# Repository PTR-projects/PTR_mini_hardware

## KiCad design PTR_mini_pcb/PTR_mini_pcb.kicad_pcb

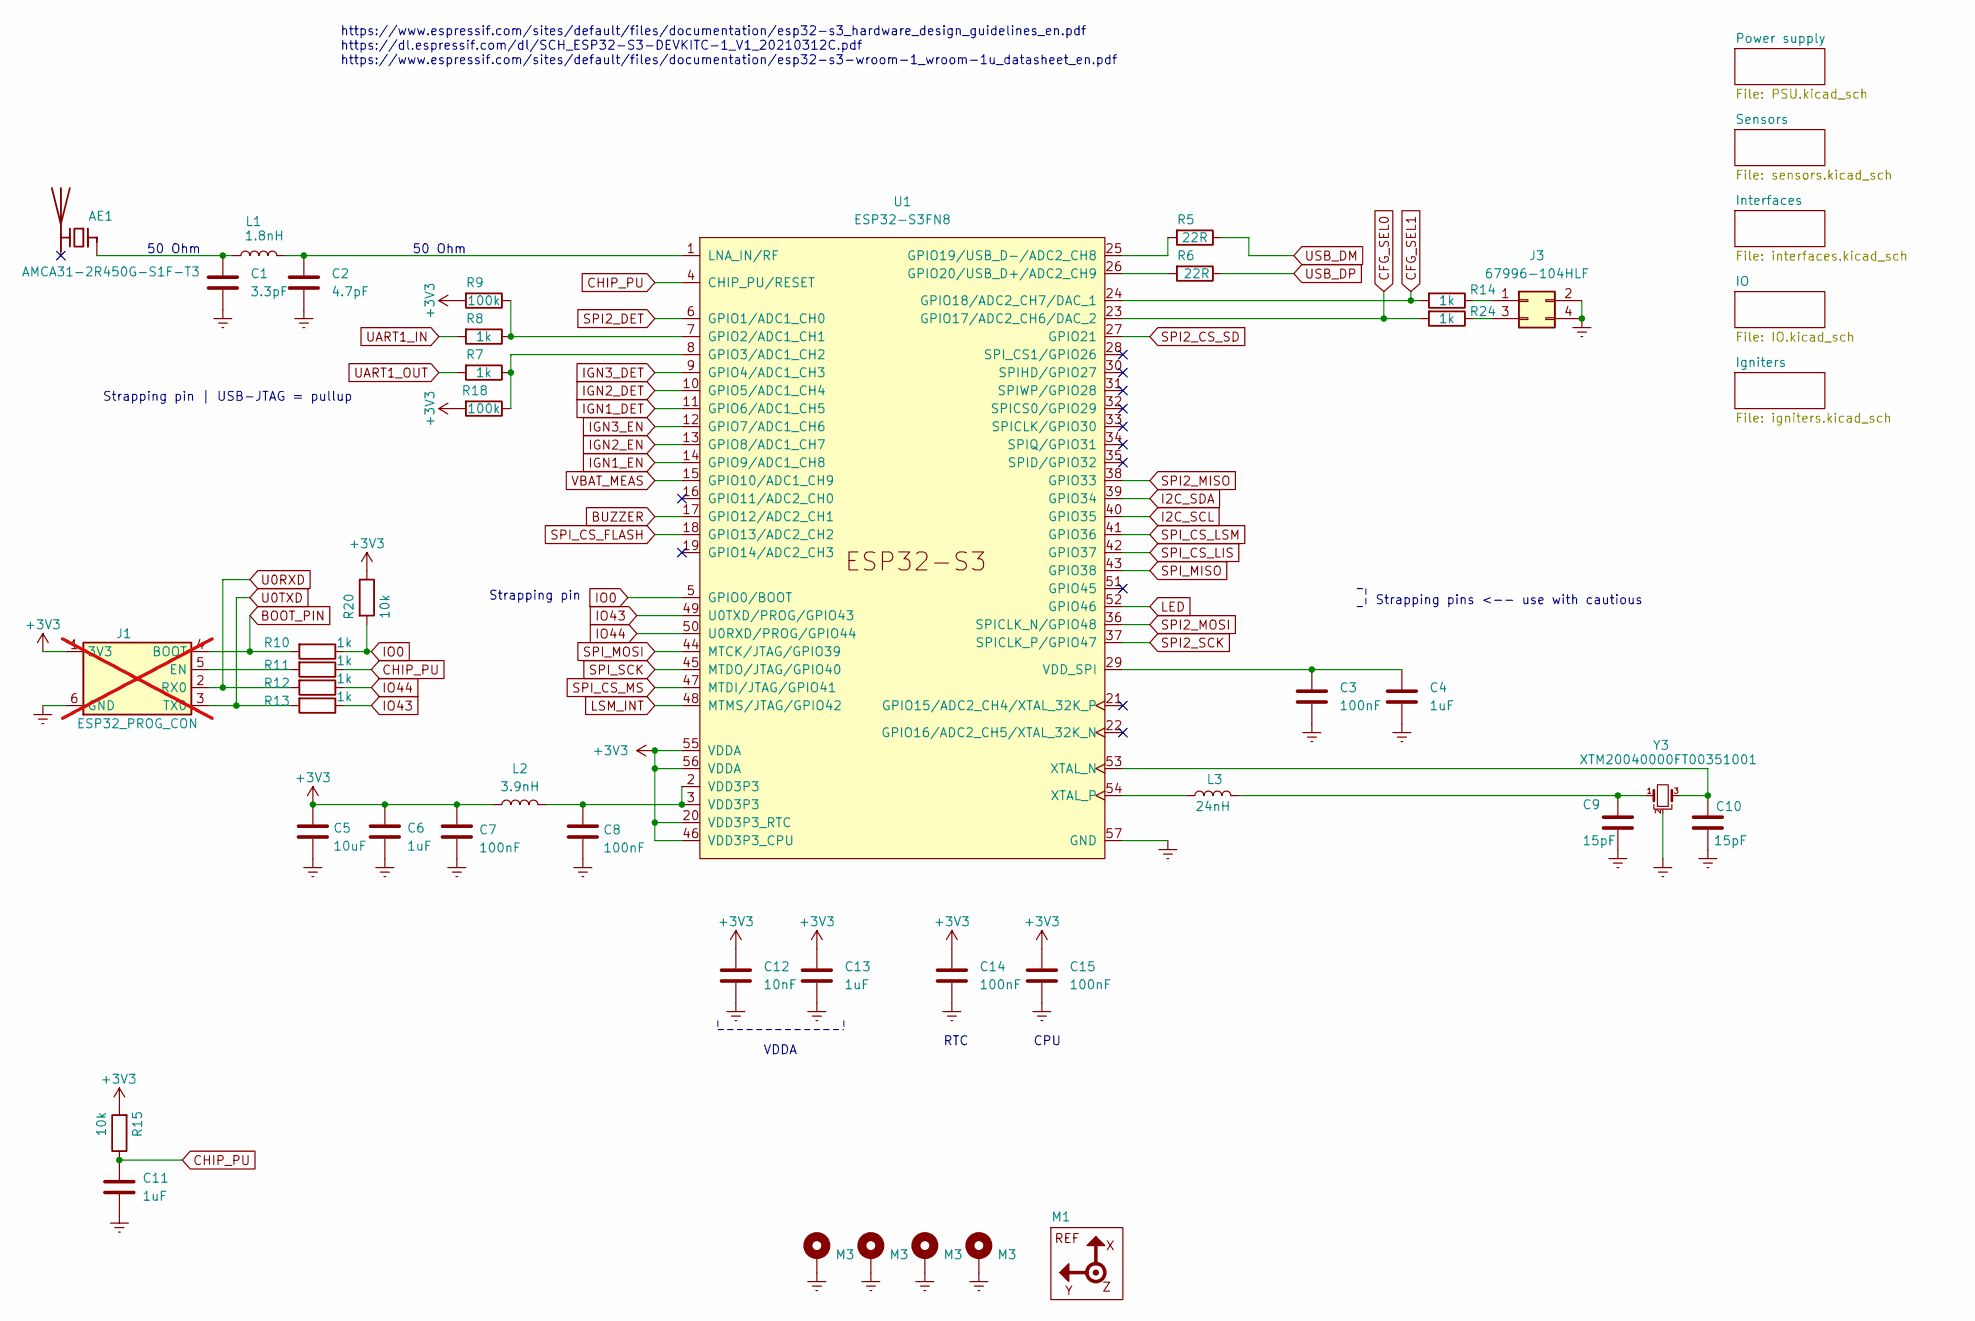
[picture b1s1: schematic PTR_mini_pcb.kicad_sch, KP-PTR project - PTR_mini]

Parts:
AE1: AMCA31-2R450G-S1F-T3
C1: 3.3pF; C_0402_1005Metric
C2: 4.7pF; C_0402_1005Metric
C3, C7, C8, C14, C15: 100nF; C_0402_1005Metric
C4, C6, C11, C13: 1uF; C_0402_1005Metric
C5: 10uF; C_0603_1608Metric
C9, C10: 15pF; C_0402_1005Metric
C12: 10nF; C_0402_1005Metric
H1, H2, H3, H4: M3; MountingHole_3.2mm_M3_DIN965_Pad
J1: ESP32_PROG_CON; PinHeader_1x06_P1.27mm_Vertical; not fitted
J3: 67996-104HLF; PinHeader_2x02_P2.54mm_Vertical
L1: 1.8nH; L_0402_1005Metric
L2: 3.9nH; L_0402_1005Metric
L3: 24nH; L_0402_1005Metric
M1: Reference_frame
R5, R6: 22R; R_0402_1005Metric
R7, R8, R10, R11, R12, R13, R14, R24: 1k; R_0402_1005Metric
R9, R18: 100k; R_0402_1005Metric
R15, R20: 10k; R_0402_1005Metric
U1: ESP32-S3FN8; ESP32-S3
Y3: XTM20040000FT00351001; Crystal_SMD_2016-4Pin_2.0x1.6mm

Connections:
+3V3: C5.1, C6.1, C7.1, C12.1, C13.1, C14.1, C15.1, J1.1 (3V3), L2.1, R9.2, R15.2, R18.2, R20.1, U1.20 (VDD3P3_RTC), U1.46 (VDD3P3_CPU), U1.55 (VDDA), U1.56 (VDDA); also elsewhere on the board
BOOT_PIN: J1.4 (BOOT), R10.2
BUZZER: U1.17 (GPIO12/ADC2_CH1); also elsewhere on the board
CFG_SEL0: R24.2, U1.23 (GPIO17/ADC2_CH6/DAC_2)
CFG_SEL1: R14.2, U1.24 (GPIO18/ADC2_CH7/DAC_1)
CHIP_PU: C11.2, R11.1, R15.1, U1.4 (CHIP_PU/RESET)
Earth: C1.2, C2.2, C3.2, C4.2, C5.2, C6.2, C7.2, C8.2, C9.1, C10.2, C11.1, C12.2, C13.2, C14.2, C15.2, H1.1 (1_1), H2.1 (1_1), H3.1 (1_1), H4.1 (1_1), J1.6 (GND), J3.2, J3.4, U1.57 (GND), Y3.2, Y3.4; also elsewhere on the board
I2C_SCL: U1.40 (GPIO35); also elsewhere on the board
I2C_SDA: U1.39 (GPIO34); also elsewhere on the board
IGN1_DET: U1.11 (GPIO6/ADC1_CH5); also elsewhere on the board
IGN1_EN: U1.14 (GPIO9/ADC1_CH8); also elsewhere on the board
IGN2_DET: U1.10 (GPIO5/ADC1_CH4); also elsewhere on the board
IGN2_EN: U1.13 (GPIO8/ADC1_CH7); also elsewhere on the board
IGN3_DET: U1.9 (GPIO4/ADC1_CH3); also elsewhere on the board
IGN3_EN: U1.12 (GPIO7/ADC1_CH6); also elsewhere on the board
IO0: R10.1, R20.2, U1.5 (GPIO0/BOOT)
IO43: R13.1, U1.49 (U0TXD/PROG/GPIO43)
IO44: R12.1, U1.50 (U0RXD/PROG/GPIO44)
LED: U1.52 (GPIO46); also elsewhere on the board
LSM_INT: U1.48 (MTMS/JTAG/GPIO42); also elsewhere on the board
unnamed: AE1.1 (FEED_1), C1.1, L1.1
unnamed: C8.1, L2.2, U1.2 (VDD3P3), U1.3 (VDD3P3)
unnamed: C9.2, L3.2, Y3.1
unnamed: J1.5 (EN), R11.2
unnamed: J3.1, R14.1
unnamed: J3.3, R24.1
unnamed: R8.1, R9.1, U1.7 (GPIO2/ADC1_CH1)
unnamed: R7.1, R18.1, U1.8 (GPIO3/ADC1_CH2)
unnamed: R5.2, U1.25 (GPIO19/USB_D-/ADC2_CH8)
unnamed: R6.2, U1.26 (GPIO20/USB_D+/ADC2_CH9)
unnamed: C2.1, L1.2, U1.1 (LNA_IN/RF)
unnamed: C3.1, C4.1, U1.29 (VDD_SPI)
unnamed: C10.1, U1.53 (XTAL_N), Y3.3
unnamed: L3.1, U1.54 (XTAL_P)
SPI2_CS_SD: U1.27 (GPIO21); also elsewhere on the board
SPI2_DET: U1.6 (GPIO1/ADC1_CH0); also elsewhere on the board
SPI2_MISO: U1.38 (GPIO33); also elsewhere on the board
SPI2_MOSI: U1.36 (SPICLK_N/GPIO48); also elsewhere on the board
SPI2_SCK: U1.37 (SPICLK_P/GPIO47); also elsewhere on the board
SPI_CS_FLASH: U1.18 (GPIO13/ADC2_CH2); also elsewhere on the board
SPI_CS_LIS: U1.42 (GPIO37); also elsewhere on the board
SPI_CS_LSM: U1.41 (GPIO36); also elsewhere on the board
SPI_CS_MS: U1.47 (MTDI/JTAG/GPIO41); also elsewhere on the board
SPI_MISO: U1.43 (GPIO38); also elsewhere on the board
SPI_MOSI: U1.44 (MTCK/JTAG/GPIO39); also elsewhere on the board
SPI_SCK: U1.45 (MTDO/JTAG/GPIO40); also elsewhere on the board
U0RXD: J1.2 (RX0), R12.2
U0TXD: J1.3 (TX0), R13.2
UART1_IN: R8.2; also elsewhere on the board
UART1_OUT: R7.2; also elsewhere on the board
USB_DM: R5.1; also elsewhere on the board
USB_DP: R6.1; also elsewhere on the board
VBAT_MEAS: U1.15 (GPIO10/ADC1_CH9); also elsewhere on the board

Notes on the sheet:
https://www.espressif.com/sites/default/files/documentation/esp32-s3_hardware_design_guidelines_en.pdf https://dl.espressif.com/dl/SCH_ESP32-S3-DEVKITC-1_V1_20210312C.pdf https://www.espressif.com/sites/default/files/documentation/esp32-s3-wroom-1_wroom-1u_datasheet_en.pdf
50 Ohm
Strapping pin
VDDA
CPU
Strapping pins <-- use with cautious
Strapping pin | USB-JTAG = pullup
RTC

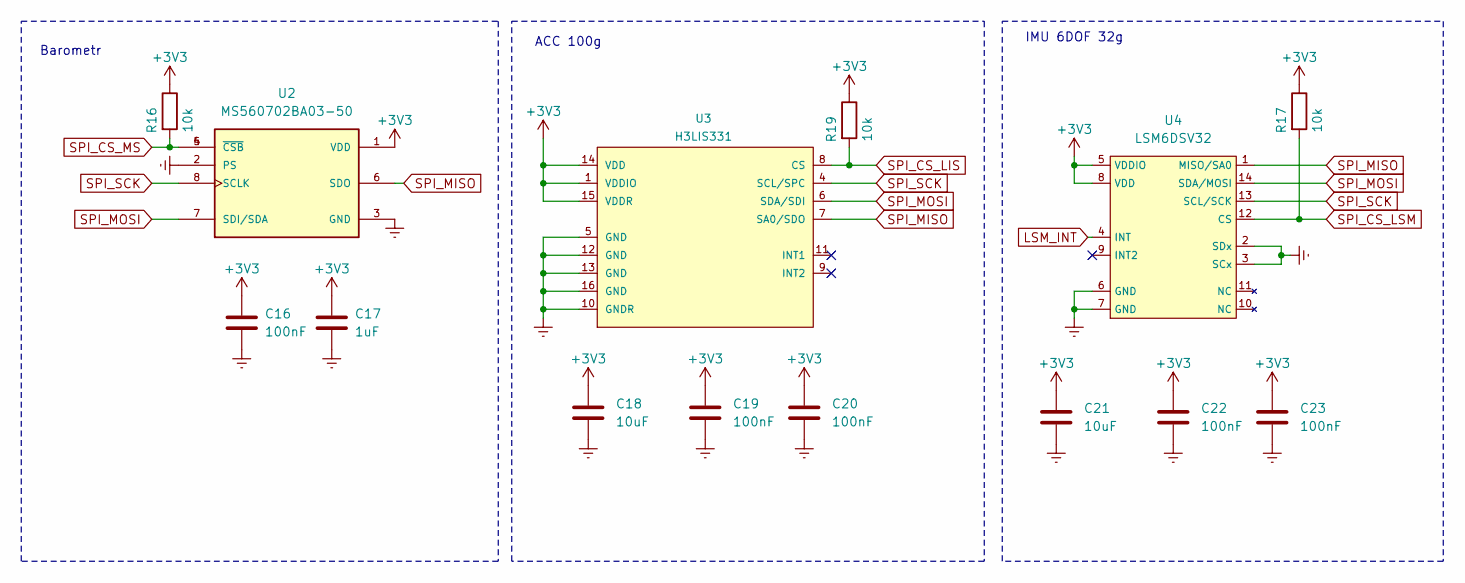
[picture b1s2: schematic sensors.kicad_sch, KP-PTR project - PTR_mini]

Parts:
C16, C19, C20, C22, C23: 100nF; C_0402_1005Metric
C17: 1uF; C_0402_1005Metric
C18, C21: 10uF; C_0603_1608Metric
R16, R17, R19: 10k; R_0402_1005Metric
U2: MS560702BA03-50; MS5607
U3: H3LIS331; LIS331
U4: LSM6DSV32; LSM6DSO32

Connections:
+3V3: C16.1, C17.1, C18.1, C19.1, C20.1, C21.1, C22.1, C23.1, R16.1, R17.1, R19.1, U2.1 (VDD), U3.1 (VDDIO), U3.14 (VDD), U3.15 (VDDR), U4.5 (VDDIO), U4.8 (VDD); also elsewhere on the board
Earth: C16.2, C17.2, C18.2, C19.2, C20.2, C21.2, C22.2, C23.2, U2.2 (PS), U2.3 (GND), U3.5 (GND), U3.10 (GNDR), U3.12 (GND), U3.13 (GND), U3.16 (GND), U4.2 (SDx), U4.3 (SCx), U4.6 (GND), U4.7 (GND); also elsewhere on the board
LSM_INT: U4.4 (INT); also elsewhere on the board
SPI_CS_LIS: R19.2, U3.8 (CS); also elsewhere on the board
SPI_CS_LSM: R17.2, U4.12 (CS); also elsewhere on the board
SPI_CS_MS: R16.2, U2.4 (~CSB), U2.5 (~CSB); also elsewhere on the board
SPI_MISO: U2.6 (SDO), U3.7 (SA0/SDO), U4.1 (MISO/SA0); also elsewhere on the board
SPI_MOSI: U2.7 (SDI/SDA), U3.6 (SDA/SDI), U4.14 (SDA/MOSI); also elsewhere on the board
SPI_SCK: U2.8 (SCLK), U3.4 (SCL/SPC), U4.13 (SCL/SCK); also elsewhere on the board

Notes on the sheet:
Barometr
IMU 6DOF 32g
ACC 100g

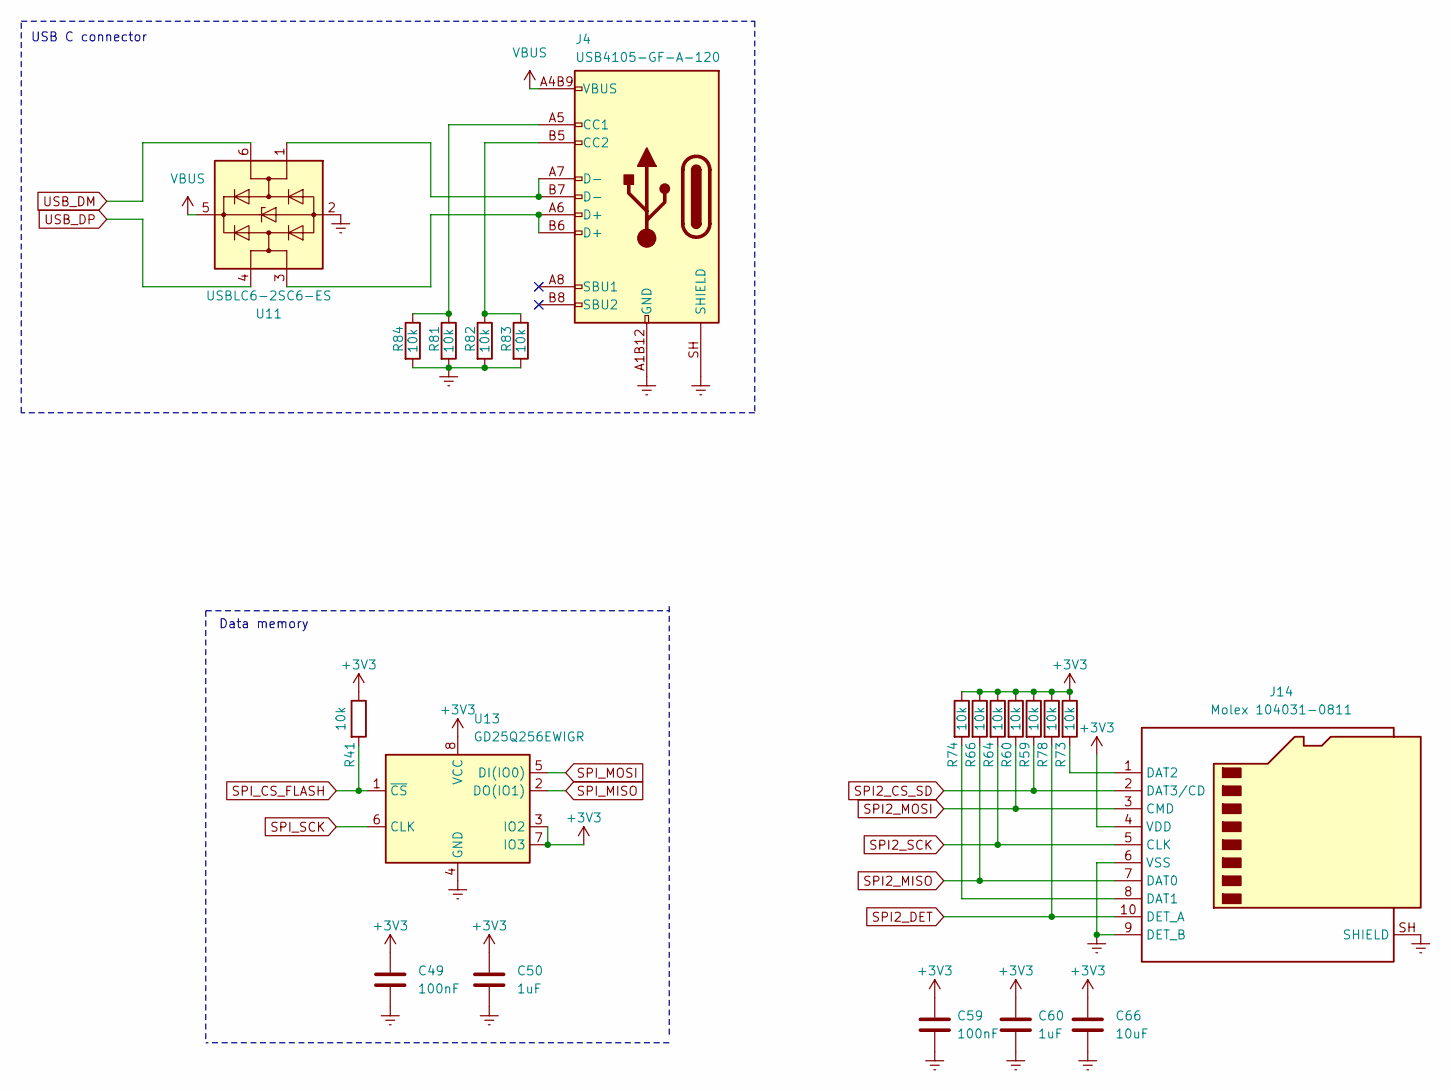
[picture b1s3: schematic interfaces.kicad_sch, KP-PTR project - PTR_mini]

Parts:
C49, C59: 100nF; C_0402_1005Metric
C50, C60: 1uF; C_0402_1005Metric
C66: 10uF; C_0805_2012Metric
J4: USB4105-GF-A-120; USB_C_16P_SMD_USB4105-GF-A
J14: Molex 104031-0811; microSD_HC_Molex_104031-0811
R41, R59, R60, R64, R66, R73, R74, R78, R81, R82, R83, R84: 10k; R_0402_1005Metric
U11: USBLC6-2SC6-ES; SOT-23-6
U13: GD25Q256EWIGR; SON127P800X600X80-9N-D

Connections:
+3V3: C49.1, C50.1, C59.1, C60.1, C66.1, J14.4 (VDD), R41.1, R59.1, R60.1, R64.1, R66.1, R73.1, R74.1, R78.1, U13.3 (IO2), U13.7 (IO3), U13.8 (VCC); also elsewhere on the board
Earth: C49.2, C50.2, C59.2, C60.2, C66.2, J4.A1B12 (GND), J4.B1A12 (GND), J4.SH (SHIELD), J14.6 (VSS), J14.9 (DET_B), J14.SH (SHIELD), R81.2, R82.2, R83.2, R84.2, U11.2 (GND), U13.4 (GND); also elsewhere on the board
unnamed: J4.A5 (CC1), R81.1, R84.1
unnamed: J4.B5 (CC2), R82.1, R83.1
unnamed: J4.A6 (D+), J4.B6 (D+), U11.3 (I/O2)
unnamed: J4.A7 (D-), J4.B7 (D-), U11.1 (I/O1)
unnamed: J14.8 (DAT1), R74.2
unnamed: J14.1 (DAT2), R73.2
SPI2_CS_SD: J14.2 (DAT3/CD), R59.2; also elsewhere on the board
SPI2_DET: J14.10 (DET_A), R78.2; also elsewhere on the board
SPI2_MISO: J14.7 (DAT0), R66.2; also elsewhere on the board
SPI2_MOSI: J14.3 (CMD), R60.2; also elsewhere on the board
SPI2_SCK: J14.5 (CLK), R64.2; also elsewhere on the board
SPI_CS_FLASH: R41.2, U13.1 (~CS); also elsewhere on the board
SPI_MISO: U13.2 (DO(IO1)); also elsewhere on the board
SPI_MOSI: U13.5 (DI(IO0)); also elsewhere on the board
SPI_SCK: U13.6 (CLK); also elsewhere on the board
USB_DM: U11.6 (I/O1); also elsewhere on the board
USB_DP: U11.4 (I/O2); also elsewhere on the board
VBUS: J4.A4B9 (VBUS), J4.B4A9 (VBUS), U11.5 (VBUS); also elsewhere on the board

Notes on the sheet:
USB C connector
Data memory

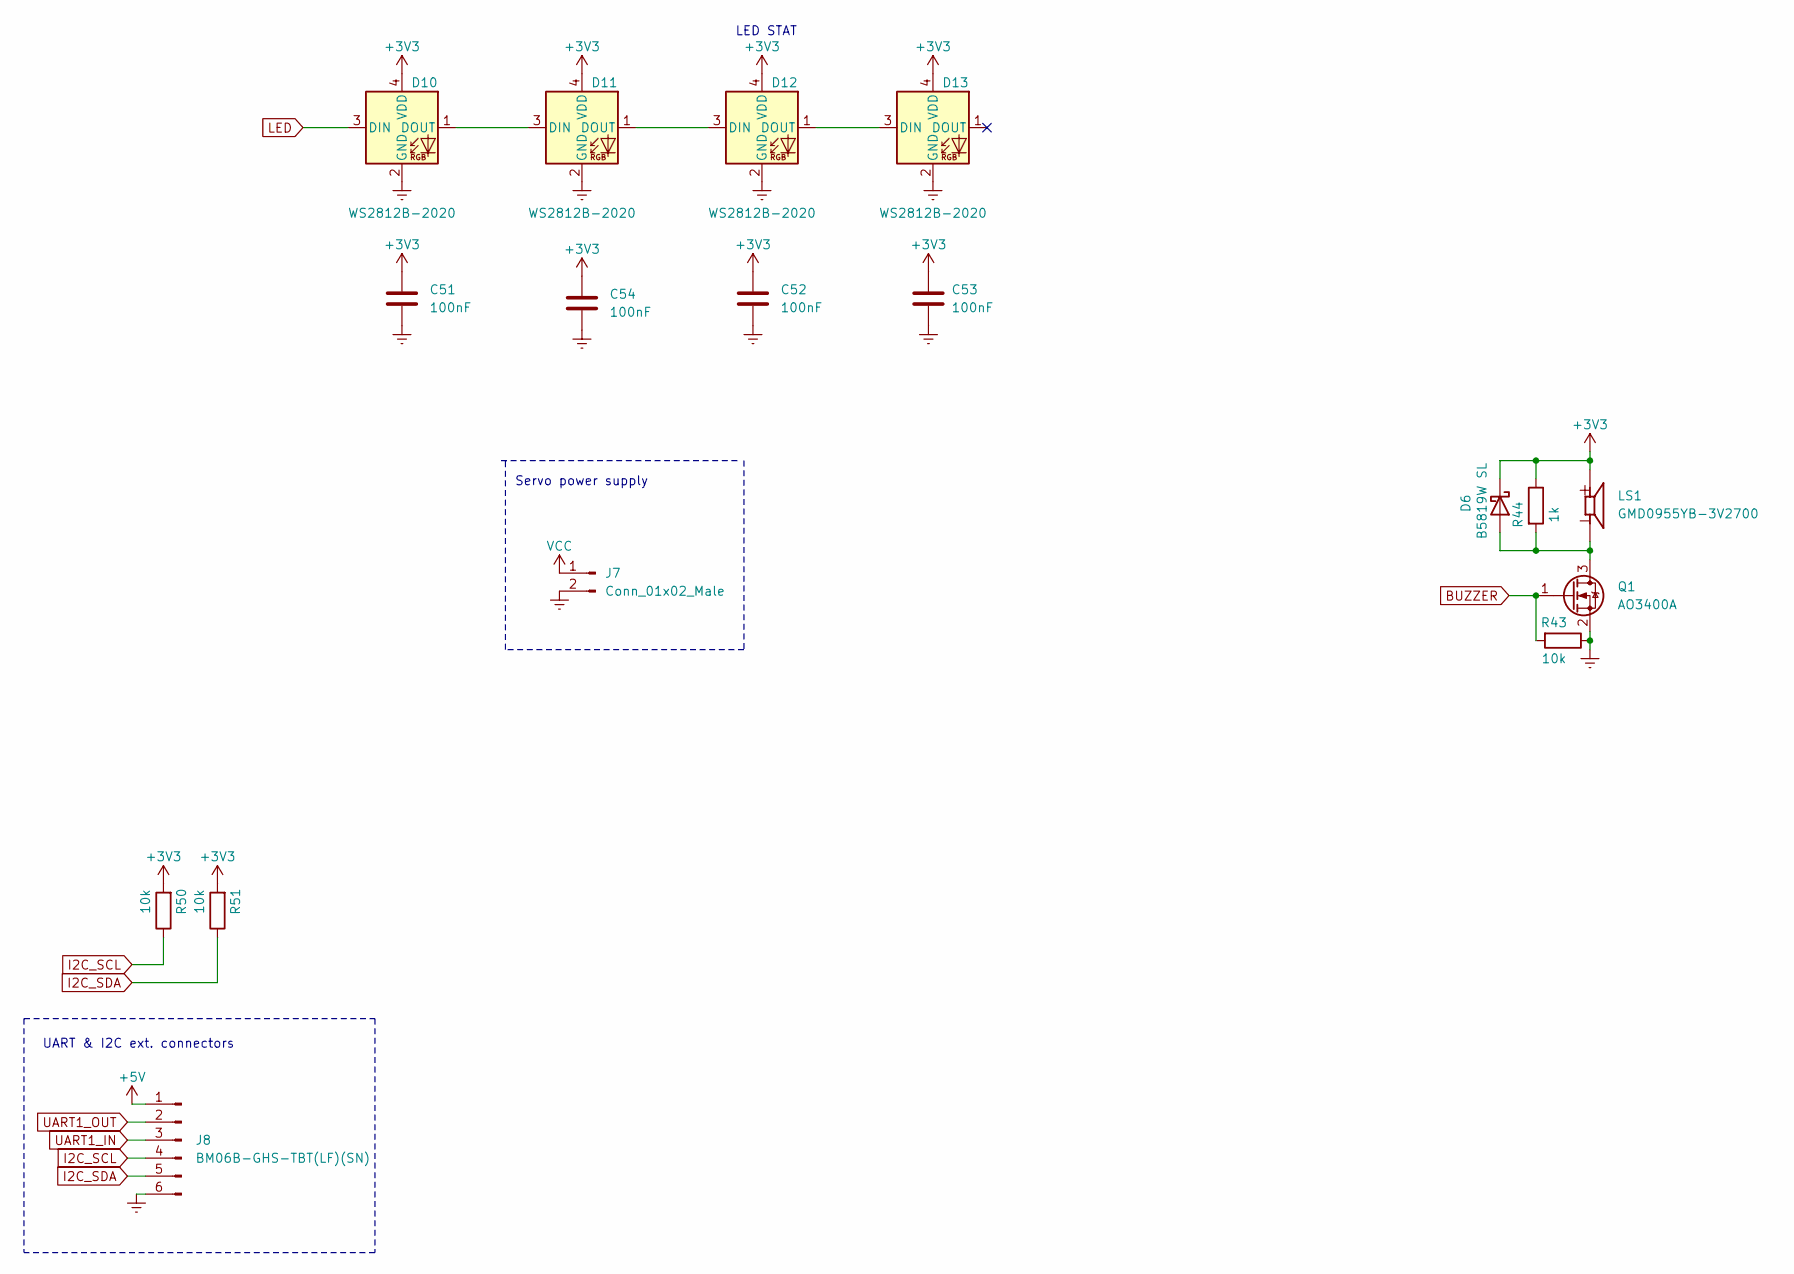
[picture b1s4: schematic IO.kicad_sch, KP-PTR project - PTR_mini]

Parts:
C51, C52, C53, C54: 100nF; C_0402_1005Metric
D6: B5819W SL; D_SOD-123
D10, D11, D12, D13: WS2812B-2020
J7: Conn_01x02_Male; TerminalBlock_TE_282834-2_1x02_P2.54mm_Horizontal
J8: BM06B-GHS-TBT(LF)(SN); JST_GH_BM06B-GHS-TBT_1x06-1MP_P1.25mm_Vertical
LS1: GMD0955YB-3V2700; MagneticBuzzer_PUI_AT-0927-TT-6-R
Q1: AO3400A; SOT-23
R43, R50, R51: 10k; R_0402_1005Metric
R44: 1k; R_0402_1005Metric

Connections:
+3V3: C51.1, C52.1, C53.1, C54.1, D6.1 (K), D10.4 (VDD), D11.4 (VDD), D12.4 (VDD), D13.4 (VDD), LS1.1 (+), R44.1, R50.2, R51.2; also elsewhere on the board
+5V: J8.1; also elsewhere on the board
BUZZER: Q1.1 (G), R43.2; also elsewhere on the board
Earth: C51.2, C52.2, C53.2, C54.2, D10.2 (GND), D11.2 (GND), D12.2 (GND), D13.2 (GND), J7.2, J8.6, Q1.2 (S), R43.1; also elsewhere on the board
I2C_SCL: J8.4, R50.1; also elsewhere on the board
I2C_SDA: J8.5, R51.1; also elsewhere on the board
LED: D10.3 (DIN); also elsewhere on the board
unnamed: D6.2 (A), LS1.2 (-), Q1.3 (D), R44.2
unnamed: D10.1 (DOUT), D11.3 (DIN)
unnamed: D11.1 (DOUT), D12.3 (DIN)
unnamed: D12.1 (DOUT), D13.3 (DIN)
UART1_IN: J8.3; also elsewhere on the board
UART1_OUT: J8.2; also elsewhere on the board
VCC: J7.1; also elsewhere on the board

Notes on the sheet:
LED STAT
Servo power supply
UART & I2C ext. connectors

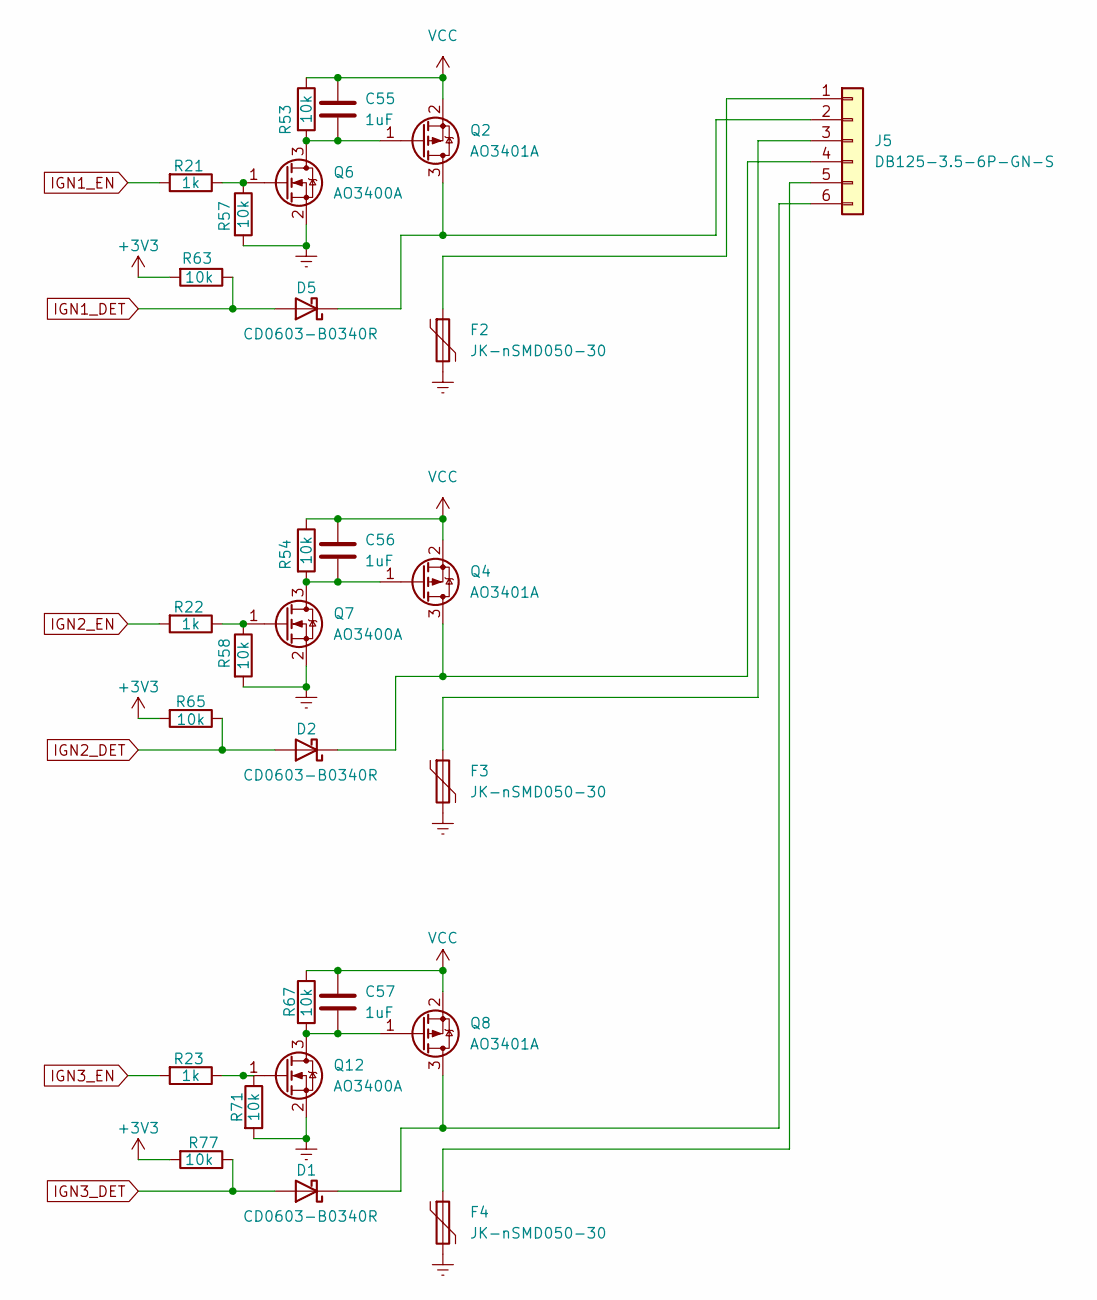
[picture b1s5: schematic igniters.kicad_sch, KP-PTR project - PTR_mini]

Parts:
C55, C56, C57: 1uF; C_0402_1005Metric
D1, D2, D5: CD0603-B0340R; D_0603_1608Metric
F2, F3, F4: JK-nSMD050-30; Fuse_1206_3216Metric
J5: DB125-3.5-6P-GN-S; TerminalBlock_Phoenix_PT-1,5-6-3.5-H_1x06_P3.50mm_Horizontal
Q2, Q4, Q8: AO3401A; SOT-23
Q6, Q7, Q12: AO3400A; SOT-23
R21, R22, R23: 1k; R_0402_1005Metric
R53, R54, R57, R58, R63, R65, R67, R71, R77: 10k; R_0402_1005Metric

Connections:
+3V3: R63.2, R65.2, R77.2; also elsewhere on the board
Earth: F2.2, F3.2, F4.2, Q6.2 (S), Q7.2 (S), Q12.2 (S), R57.2, R58.2, R71.2; also elsewhere on the board
IGN1_DET: D5.2 (A), R63.1; also elsewhere on the board
IGN1_EN: R21.2; also elsewhere on the board
IGN2_DET: D2.2 (A), R65.1; also elsewhere on the board
IGN2_EN: R22.2; also elsewhere on the board
IGN3_DET: D1.2 (A), R77.1; also elsewhere on the board
IGN3_EN: R23.2; also elsewhere on the board
unnamed: D1.1 (K), J5.6, Q8.3 (D)
unnamed: D2.1 (K), J5.4, Q4.3 (D)
unnamed: D5.1 (K), J5.2, Q2.3 (D)
unnamed: F2.1, J5.1
unnamed: F3.1, J5.3
unnamed: F4.1, J5.5
unnamed: C55.2, Q2.1 (G), Q6.3 (D), R53.2
unnamed: C56.2, Q4.1 (G), Q7.3 (D), R54.2
unnamed: Q6.1 (G), R21.1, R57.1
unnamed: Q7.1 (G), R22.1, R58.1
unnamed: C57.2, Q8.1 (G), Q12.3 (D), R67.2
unnamed: Q12.1 (G), R23.1, R71.1
VCC: C55.1, C56.1, C57.1, Q2.2 (S), Q4.2 (S), Q8.2 (S), R53.1, R54.1, R67.1; also elsewhere on the board

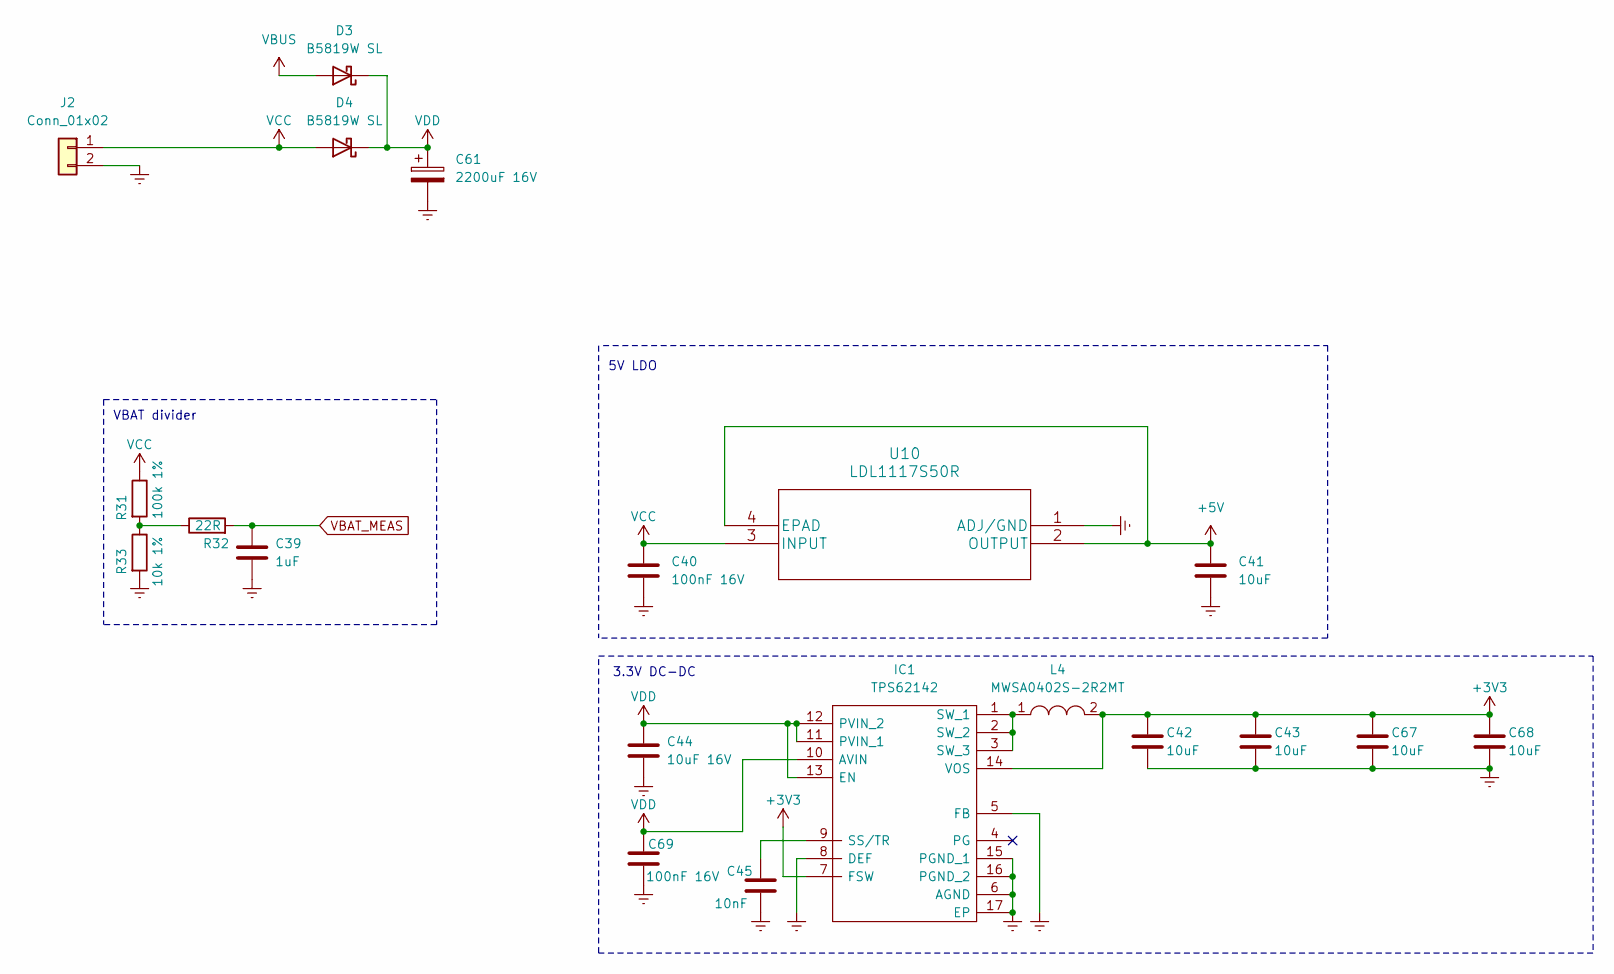
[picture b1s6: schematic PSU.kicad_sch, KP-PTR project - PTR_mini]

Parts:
C39: 1uF; C_0402_1005Metric
C40, C69: 100nF 16V; C_0402_1005Metric
C41, C42, C43, C67, C68: 10uF; C_0805_2012Metric
C44: 10uF 16V; C_0805_2012Metric
C45: 10nF; C_0402_1005Metric
C61: 2200uF 16V; CP_Radial_D10.0mm_P5.00mm
D3, D4: B5819W SL; D_SOD-123
IC1: TPS62142; QFN50P300X300X100-17N-D; Manufacturer_Part_Number TPS62140ARGTR; Mouser Part Number 595-TPS62140ARGTR
J2: Conn_01x02; TerminalBlock_TE_282834-2_1x02_P2.54mm_Horizontal
L4: MWSA0402S-2R2MT; INDPM4442X200N
R31: 100k 1%; R_0402_1005Metric
R32: 22R; R_0402_1005Metric
R33: 10k 1%; R_0402_1005Metric
U10: LDL1117S50R; AZ1117CH-5.0TRG1

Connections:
+3V3: C42.1, C43.1, C67.1, C68.1, IC1.7 (FSW), IC1.14 (VOS), L4.2; also elsewhere on the board
+5V: C41.1, U10.2 (OUTPUT), U10.4 (EPAD); also elsewhere on the board
Earth: C39.2, C40.2, C41.2, C42.2, C43.2, C44.2, C45.1, C61.2, C67.2, C68.2, C69.2, IC1.5 (FB), IC1.6 (AGND), IC1.8 (DEF), IC1.15 (PGND_1), IC1.16 (PGND_2), IC1.17 (EP), J2.2, R33.2, U10.1 (ADJ/GND); also elsewhere on the board
unnamed: C45.2, IC1.9 (SS/TR)
unnamed: IC1.1 (SW_1), IC1.2 (SW_2), IC1.3 (SW_3), L4.1
unnamed: R31.2, R32.1, R33.1
VBAT_MEAS: C39.1, R32.2; also elsewhere on the board
VBUS: D3.2 (A); also elsewhere on the board
VCC: C40.1, D4.2 (A), J2.1, R31.1, U10.3 (INPUT); also elsewhere on the board
VDD: C44.1, C61.1, C69.1, D3.1 (K), D4.1 (K), IC1.10 (AVIN), IC1.11 (PVIN_1), IC1.12 (PVIN_2), IC1.13 (EN)

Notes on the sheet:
VBAT divider
5V LDO
3.3V DC-DC

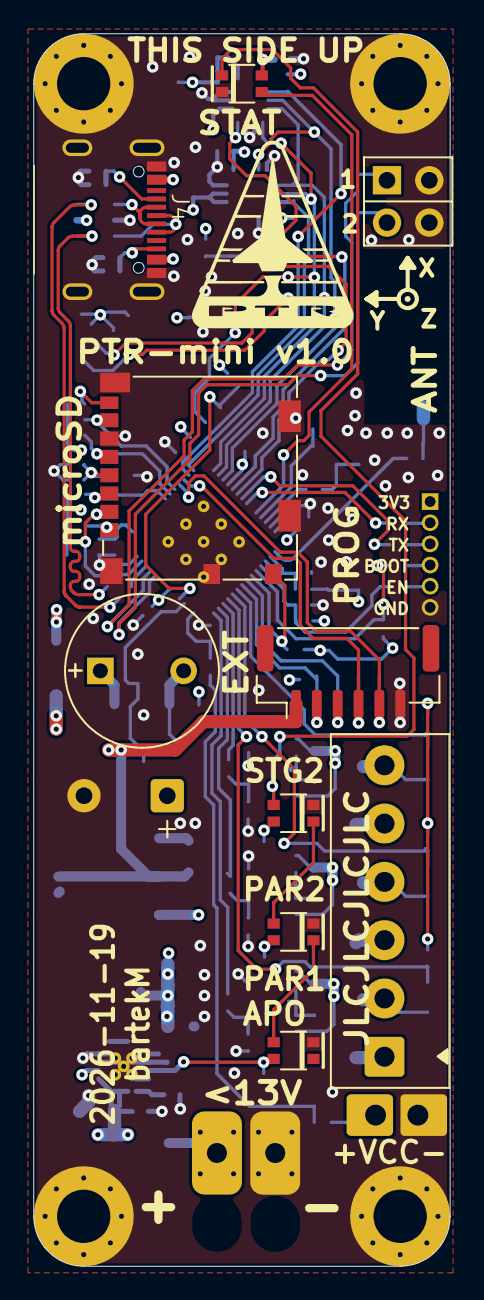
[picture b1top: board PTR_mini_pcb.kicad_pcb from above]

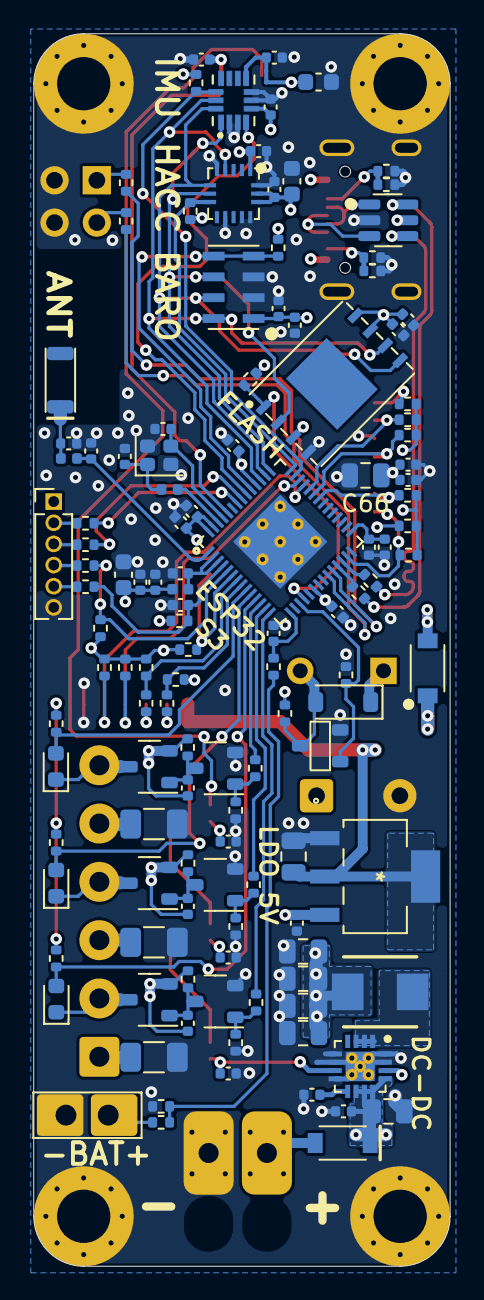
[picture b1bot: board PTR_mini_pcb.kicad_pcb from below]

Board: 4 copper layers, 25.0 x 74.0 mm, 142 parts (125 on the bottom side), 82 nets.

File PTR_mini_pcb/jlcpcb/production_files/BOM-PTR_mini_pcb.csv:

Comment,Designator,Footprint,LCSC,Quantity
1.8nH,L1,L_0402_1005Metric,C77107,1
100k,"R18,R9",R_0402_1005Metric,C25741,2
100k 1%,R31,R_0402_1005Metric,C25741,1
100nF,"C14,C15,C16,C19,C20,C22,C23,C3,C49,C51,C52,C53,C54,C59,C7,C8",C_0402_1005Metric,C1525,16
100nF 16V,"C40,C69",C_0402_1005Metric,C1525,2
10k,"R15,R16,R17,R19,R20,R41,R43,R50,R51,R53,R54,R57,R58,R59,R60,R63,R64,R65,R66,R67,R71,R73,R74,R77,R78,R81,R82,R83,R84",R_0402_1005Metric,C25744,29
10k 1%,R33,R_0402_1005Metric,C25744,1
10nF,"C12,C45",C_0402_1005Metric,C15195,2
10uF,"C41,C42,C43,C66,C67,C68",C_0805_2012Metric,C3039694,6
10uF,"C18,C21,C5",C_0603_1608Metric,C96446,3
10uF 16V,C44,C_0805_2012Metric,C3039694,1
15pF,"C10,C9",C_0402_1005Metric,C1548,2
1k,"R10,R11,R12,R13,R14,R21,R22,R23,R24,R44,R7,R8",R_0402_1005Metric,C11702,12
1uF,"C11,C13,C17,C39,C4,C50,C55,C56,C57,C6,C60",C_0402_1005Metric,C52923,11
22R,"R32,R5,R6",R_0402_1005Metric,C25092,3
24nH,L3,L_0402_1005Metric,C74301,1
3.3pF,C1,C_0402_1005Metric,C76906,1
3.9nH,L2,L_0402_1005Metric,C3911386,1
4.7pF,C2,C_0402_1005Metric,C161327,1
67996-104HLF,J3,PinHeader_2x02_P2.54mm_Vertical,C3328102,1
AMCA31-2R450G-S1F-T3,AE1,AMCA31-2R450G-S1F-T3,C3283994,1
AO3400A,"Q1,Q12,Q6,Q7",SOT-23,C20917,4
AO3401A,"Q2,Q4,Q8",SOT-23,C15127,3
B5819W SL,"D3,D4,D6",D_SOD-123,C8598,3
BM06B-GHS-TBT(LF)(SN),J8,JST_GH_BM06B-GHS-TBT_1x06-1MP_P1.25mm_Vertical,C189892,1
CD0603-B0340R,"D1,D2,D5",D_0603_1608Metric,C482684,3
DB125-3.5-6P-GN-S,J5,"TerminalBlock_Phoenix_PT-1,5-6-3.5-H_1x06_P3.50mm_Horizontal",C5290323,1
ESP32-S3FN8,U1,ESP32-S3,C2913196,1
GD25Q256EWIGR,U13,SON127P800X600X80-9N-D,C6564321,1
GMD0955YB-3V2700,LS1,MagneticBuzzer_PUI_AT-0927-TT-6-R,C252933,1
H3LIS331,U3,LIS331,C2655074,1
JK-nSMD050-30,"F2,F3,F4",Fuse_1206_3216Metric,C720075,3
LDL1117S50R,U10,AZ1117CH-5.0TRG1,C970558,1
LSM6DSV32,U4,LSM6DSO32,C22461202,1
MS560702BA03-50,U2,MS5607,C97627,1
MWSA0402S-2R2MT,L4,INDPM4442X200N,C408335,1
Molex 104031-0811,J14,microSD_HC_Molex_104031-0811,C585350,1
TPS62142,IC1,QFN50P300X300X100-17N-D,C129331,1
USB4105-GF-A-120,J4,USB_C_16P_SMD_USB4105-GF-A,C5184243,1
USBLC6-2SC6-ES,U11,SOT-23-6,C5180249,1
WS2812B-2020,"D10,D11,D12,D13",WS2812B-2020,C52917434,4
XTM20040000FT00351001,Y3,Crystal_SMD_2016-4Pin_2.0x1.6mm,C37635335,1
2200uF 16V,C61,CP_Radial_D10.0mm_P5.00mm,,1
